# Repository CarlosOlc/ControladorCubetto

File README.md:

# ControladorCubetto

Projeto Realizado durante bacharelado em Ciência da Computação.

Proposta de uma Plataforma de Apoio ao Aprendizado do Pensamento Computacional utilizando Robótica e Programação Tangível.

Através de um sólido estudo referente a robótica educacional, programação tangível, aprendizagem algorítmica e sócio-construtivismo, foi possível compreender as necessidades que uma plataforma para o apoio ao ensino do pensamento computacional necessita para ser efetiva em sua aplicação. Tendo isso em vista, desenvolveu-se essa plataforma utilizando o Arduino, que é um microcontrolador caracterizado como open-source, e também o uso de impressão 3D. Além disso, foi esquematizada e impressa uma placa de circuito eletrônico, denominada de controladora, que compõem parte dessa plataforma. Constatou-se, após diversos testes, que a plataforma se demonstrou funcional e que, como próximo passo a ser tomado, é necessário executar testes com alunos - que não foi possível devido a atual pandemia (2020). Por fim, esse trabalho buscou contribuir para o apoio ao aprendizado do pensamento computacional, uma vez   que   proveu   de   ferramentas   necessárias   para   tal.

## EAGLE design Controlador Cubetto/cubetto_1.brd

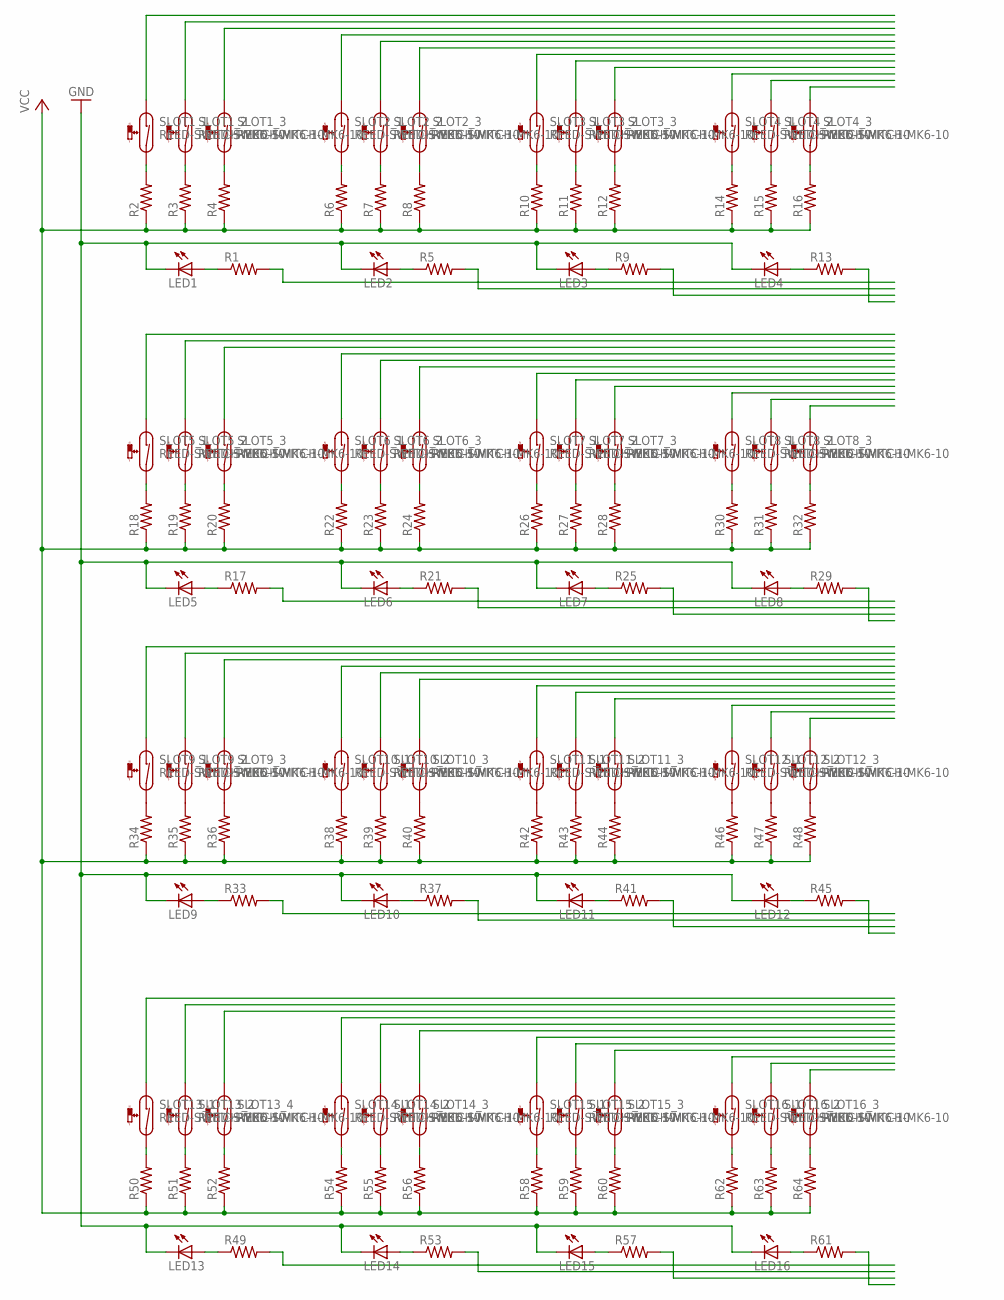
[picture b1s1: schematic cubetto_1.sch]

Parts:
LED1, LED2, LED3, LED4, LED5, LED6, LED7, LED8, LED9, LED10, LED11, LED12, LED13, LED14, LED15, LED16: LED3MM
R1, R2, R3, R4, R5, R6, R7, R8, R9, R10, R11, R12, R13, R14, R15, R16, R17, R18, R19, R20, R21, R22, R23, R24, R25, R26, R27, R28, R29, R30, R31, R32, R33, R34, R35, R36, R37, R38, R39, R40, R41, R42, R43, R44, R45, R46, R47, R48, R49, R50, R51, R52, R53, R54, R55, R56, R57, R58, R59, R60, R61, R62, R63, R64: R-US_0207/10; 0207/10
SLOT1_1, SLOT1_2, SLOT1_3, SLOT2_1, SLOT2_2, SLOT2_3, SLOT3_1, SLOT3_2, SLOT3_3, SLOT4_1, SLOT4_2, SLOT4_3, SLOT5_1, SLOT5_2, SLOT5_3, SLOT6_1, SLOT6_2, SLOT6_3, SLOT7_1, SLOT7_2, SLOT7_3, SLOT8_1, SLOT8_2, SLOT8_3, SLOT9_1, SLOT9_2, SLOT9_3, SLOT10_1, SLOT10_2, SLOT10_3, SLOT11_1, SLOT11_2, SLOT11_3, SLOT12_1, SLOT12_2, SLOT12_3, SLOT13_1, SLOT13_2, SLOT13_4, SLOT14_1, SLOT14_2, SLOT14_3, SLOT15_1, SLOT15_2, SLOT15_3, SLOT16_1, SLOT16_2, SLOT16_3: REED-SWITCH-MK6-10; MK6-10

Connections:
GND: LED1.K (C), LED2.K (C), LED3.K (C), LED4.K (C), LED5.K (C), LED6.K (C), LED7.K (C), LED8.K (C), LED9.K (C), LED10.K (C), LED11.K (C), LED12.K (C), LED13.K (C), LED14.K (C), LED15.K (C), LED16.K (C)
unnamed: LED1.A, R1.1
unnamed: R2.2, SLOT1_1.2
unnamed: R3.2, SLOT1_2.2
unnamed: R4.2, SLOT1_3.2
unnamed: LED2.A, R5.1
unnamed: R6.2, SLOT2_1.2
unnamed: R7.2, SLOT2_2.2
unnamed: R8.2, SLOT2_3.2
unnamed: LED3.A, R9.1
unnamed: R10.2, SLOT3_1.2
unnamed: R11.2, SLOT3_2.2
unnamed: R12.2, SLOT3_3.2
unnamed: LED4.A, R13.1
unnamed: R14.2, SLOT4_1.2
unnamed: R15.2, SLOT4_2.2
unnamed: R16.2, SLOT4_3.2
unnamed: LED5.A, R17.1
unnamed: R18.2, SLOT5_1.2
unnamed: R19.2, SLOT5_2.2
unnamed: R20.2, SLOT5_3.2
unnamed: LED6.A, R21.1
unnamed: R22.2, SLOT6_1.2
unnamed: R23.2, SLOT6_2.2
unnamed: R24.2, SLOT6_3.2
unnamed: LED7.A, R25.1
unnamed: R26.2, SLOT7_1.2
unnamed: R27.2, SLOT7_2.2
unnamed: R28.2, SLOT7_3.2
unnamed: LED8.A, R29.1
unnamed: R30.2, SLOT8_1.2
unnamed: R31.2, SLOT8_2.2
unnamed: R32.2, SLOT8_3.2
unnamed: LED9.A, R33.1
unnamed: R34.2, SLOT9_1.2
unnamed: R35.2, SLOT9_2.2
unnamed: R36.2, SLOT9_3.2
unnamed: LED10.A, R37.1
unnamed: R38.2, SLOT10_1.2
unnamed: R39.2, SLOT10_2.2
unnamed: R40.2, SLOT10_3.2
unnamed: LED11.A, R41.1
unnamed: R42.2, SLOT11_1.2
unnamed: R43.2, SLOT11_2.2
unnamed: R44.2, SLOT11_3.2
unnamed: LED12.A, R45.1
unnamed: R46.2, SLOT12_1.2
unnamed: R47.2, SLOT12_2.2
unnamed: R48.2, SLOT12_3.2
unnamed: LED13.A, R49.1
unnamed: R50.2, SLOT13_1.2
unnamed: R51.2, SLOT13_2.2
unnamed: R52.2, SLOT13_4.2
unnamed: LED14.A, R53.1
unnamed: R54.2, SLOT14_1.2
unnamed: R55.2, SLOT14_2.2
unnamed: R56.2, SLOT14_3.2
unnamed: LED15.A, R57.1
unnamed: R58.2, SLOT15_1.2
unnamed: R59.2, SLOT15_2.2
unnamed: R60.2, SLOT15_3.2
unnamed: LED16.A, R61.1
unnamed: R62.2, SLOT16_1.2
unnamed: R63.2, SLOT16_2.2
unnamed: R64.2, SLOT16_3.2
VCC: R2.1, R3.1, R4.1, R6.1, R7.1, R8.1, R10.1, R11.1, R12.1, R14.1, R15.1, R16.1, R18.1, R19.1, R20.1, R22.1, R23.1, R24.1, R26.1, R27.1, R28.1, R30.1, R31.1, R32.1, R34.1, R35.1, R36.1, R38.1, R39.1, R40.1, R42.1, R43.1, R44.1, R46.1, R47.1, R48.1, R50.1, R51.1, R52.1, R54.1, R55.1, R56.1, R58.1, R59.1, R60.1, R62.1, R63.1, R64.1

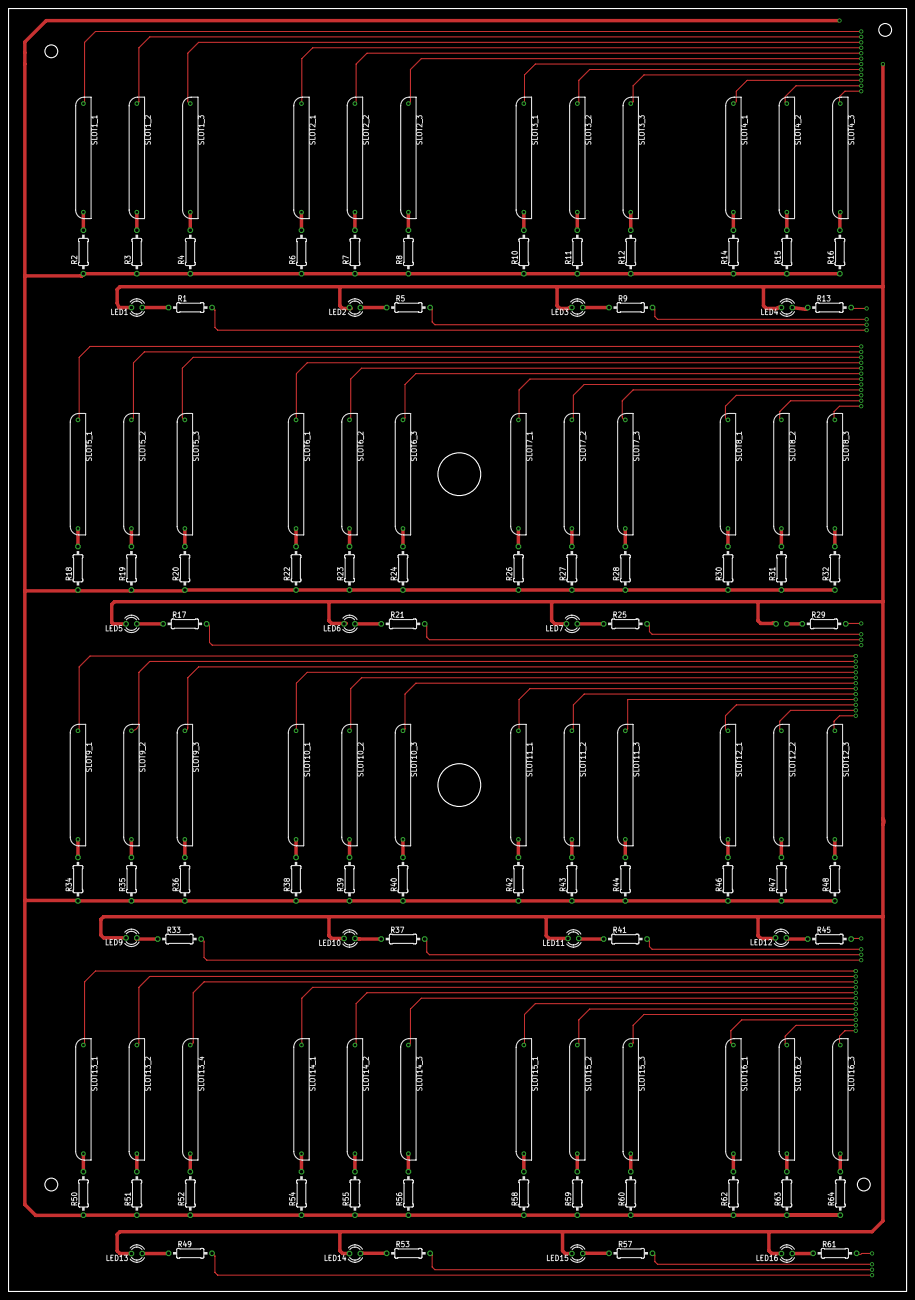
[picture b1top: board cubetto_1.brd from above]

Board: 2 copper layers, 210.0 x 300.0 mm, 128 parts (1 on the bottom side), 66 nets.

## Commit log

2020-08-05 Codigos de teste
2020-08-07 Placa controladora
    Feito no EAGLE 8.6.3
2020-08-10 add gerber file
2020-09-03 Teste Robo
2020-09-06 Atualização Codigo Teste Robo
2020-11-18 update placa
2020-11-18 codigo controladora
2020-11-18 Codigo escrever no cartao
2020-11-18 peças
2020-11-18 case do robo
2020-11-18 caixa controladora
2020-11-18 codigo robo 2
